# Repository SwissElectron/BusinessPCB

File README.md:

# BusinessPCB
Business Card PCB with NFC capabilities

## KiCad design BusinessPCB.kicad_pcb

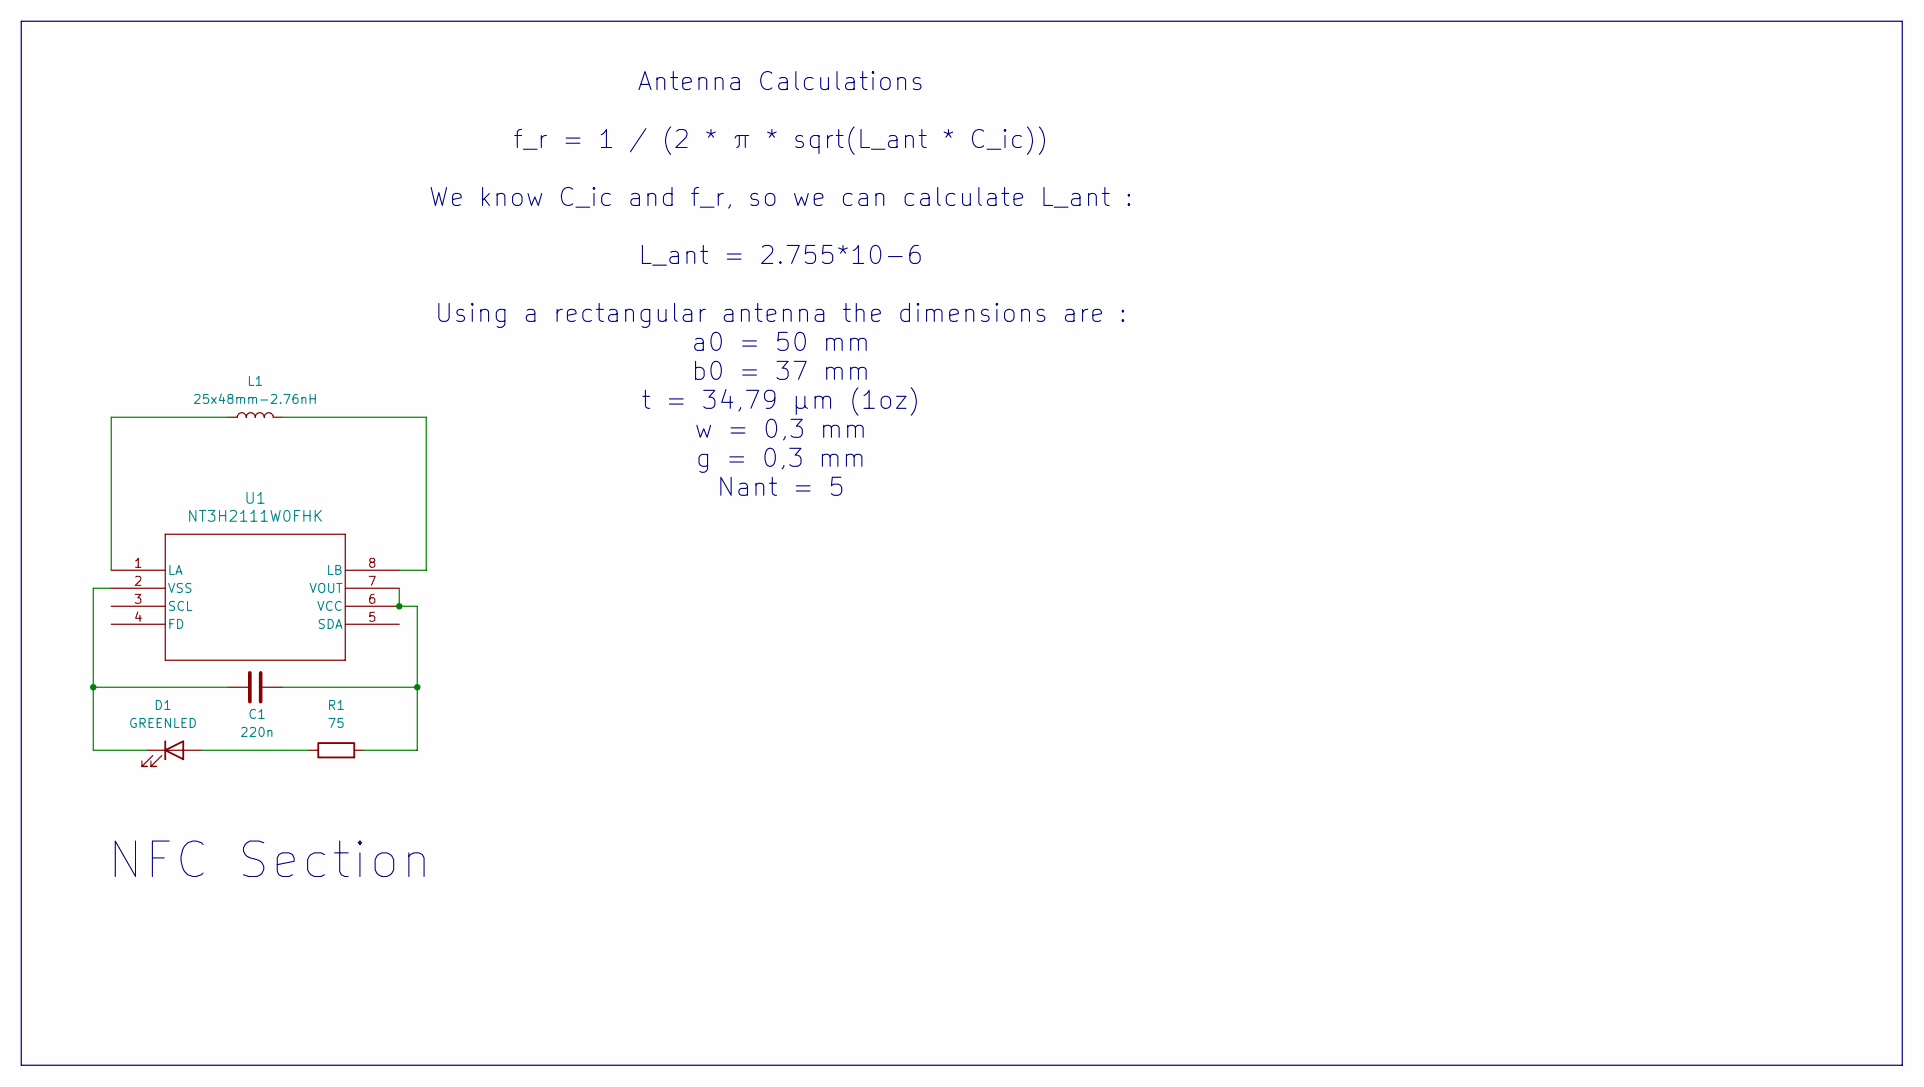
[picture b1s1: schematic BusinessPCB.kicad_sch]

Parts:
C1: 220n; C_0402_1005Metric; PART_NUMBER 01016D224MAT2A
D1: GREENLED; LED_0402_1005Metric; PART_NUMBER SM0402GC
L1: 25x48mm-2.76nH; NFC 2.76 nH
R1: 75; R_0402_1005Metric; PART_NUMBER 0402WGF750JTCE
U1: NT3H2111W0FHK; XQFN8_NT3H2111_NXP; PART_NUMBER NT3H2111W0FHK

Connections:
unnamed: D1.2 (A), R1.1
unnamed: C1.2, D1.1 (K), U1.2 (VSS)
unnamed: L1.1, U1.1 (LA)
unnamed: L1.2, U1.8 (LB)
unnamed: C1.1, R1.2, U1.6 (VCC), U1.7 (VOUT)

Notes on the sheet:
Antenna Calculations f_r = 1 / (2 * π * sqrt(L_ant * C_ic)) We know C_ic and f_r, so we can calculate L_ant : L_ant = 2.755*10-6 Using a rectangular antenna the dimensions are : a0 = 50 mm b0 = 37 mm t = 34,79 µm (1oz) w = 0,3 mm g = 0,3 mm Nant = 5
NFC Section

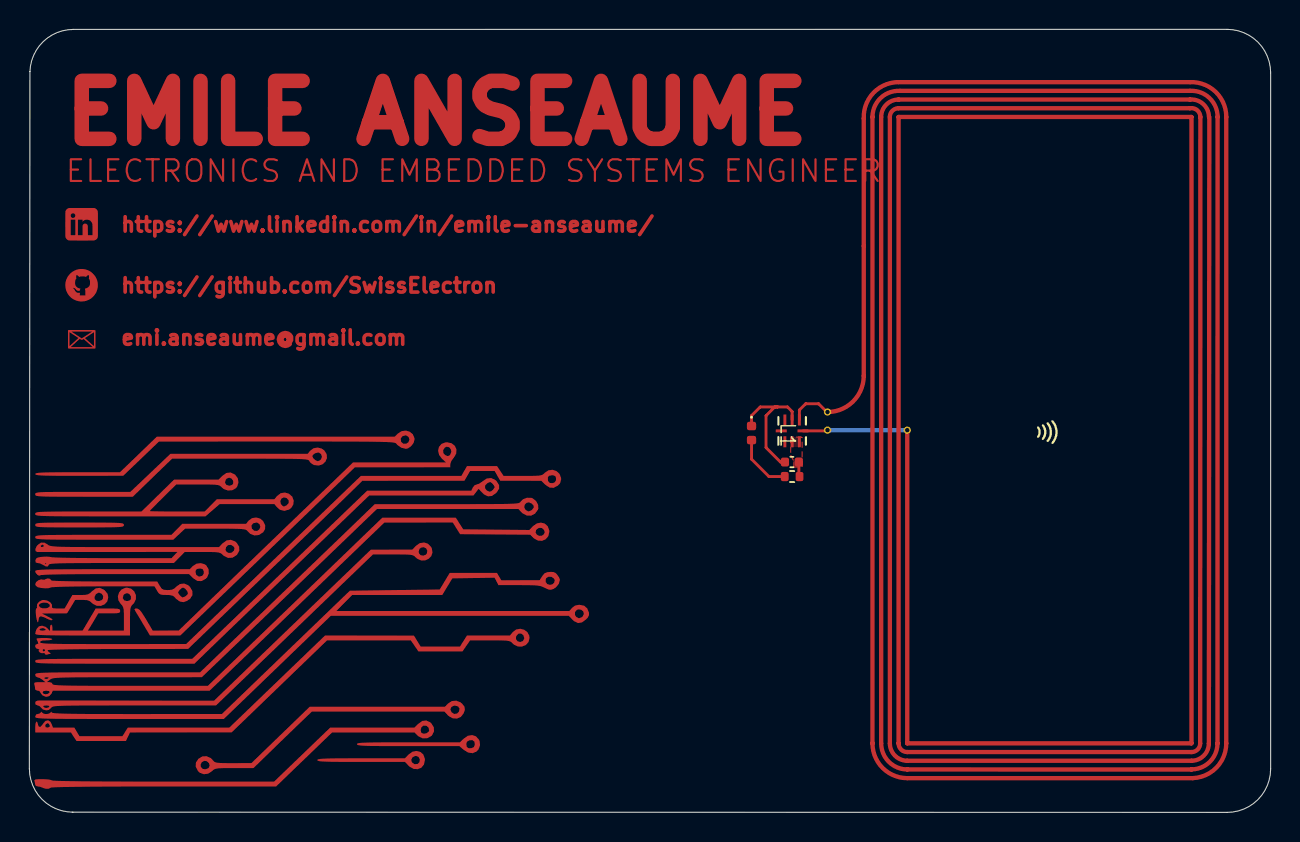
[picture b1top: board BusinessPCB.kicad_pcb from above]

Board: 2 copper layers, 85.6 x 54.0 mm, 5 parts (0 on the bottom side), 5 nets.

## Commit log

2024-10-13 added gitignore
2024-10-13 added list to gitignore
2024-10-13 modified gitignore file
2024-10-13 Added design files
